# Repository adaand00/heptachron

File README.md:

```
    __  ____________  _________   ________  ______  ____  _   __
   / / / / ____/ __ \/_  __/   | / ____/ / / / __ \/ __ \/ | / /
  / /_/ / __/ / /_/ / / / / /| |/ /   / /_/ / /_/ / / / /  |/ / 
 / __  / /___/ ____/ / / / ___ / /___/ __  / _, _/ /_/ / /|  /  
/_/ /_/_____/_/     /_/ /_/  |_\____/_/ /_/_/ |_|\____/_/ |_/   
```                                                                
## Heptachron - 7 segment LED wrist watch
Latest prototype:

### Concepts and ideas

### Features
 - [x] 4 digits (hours and minutes)
 - [x] Seconds displayed in binary (6 bits)
 - [x] Always-on display
 - [x] Rechargeable battery
 - [x] Magnetic charger
 - [ ] Long battery life
 - [x] Megatron
 - [x] Not waterproof
 - [ ] Very accurate

### Contributors
Adam Anderson: Electronics, programming

Gustav Abrahamsson: Electronics, mechanical design

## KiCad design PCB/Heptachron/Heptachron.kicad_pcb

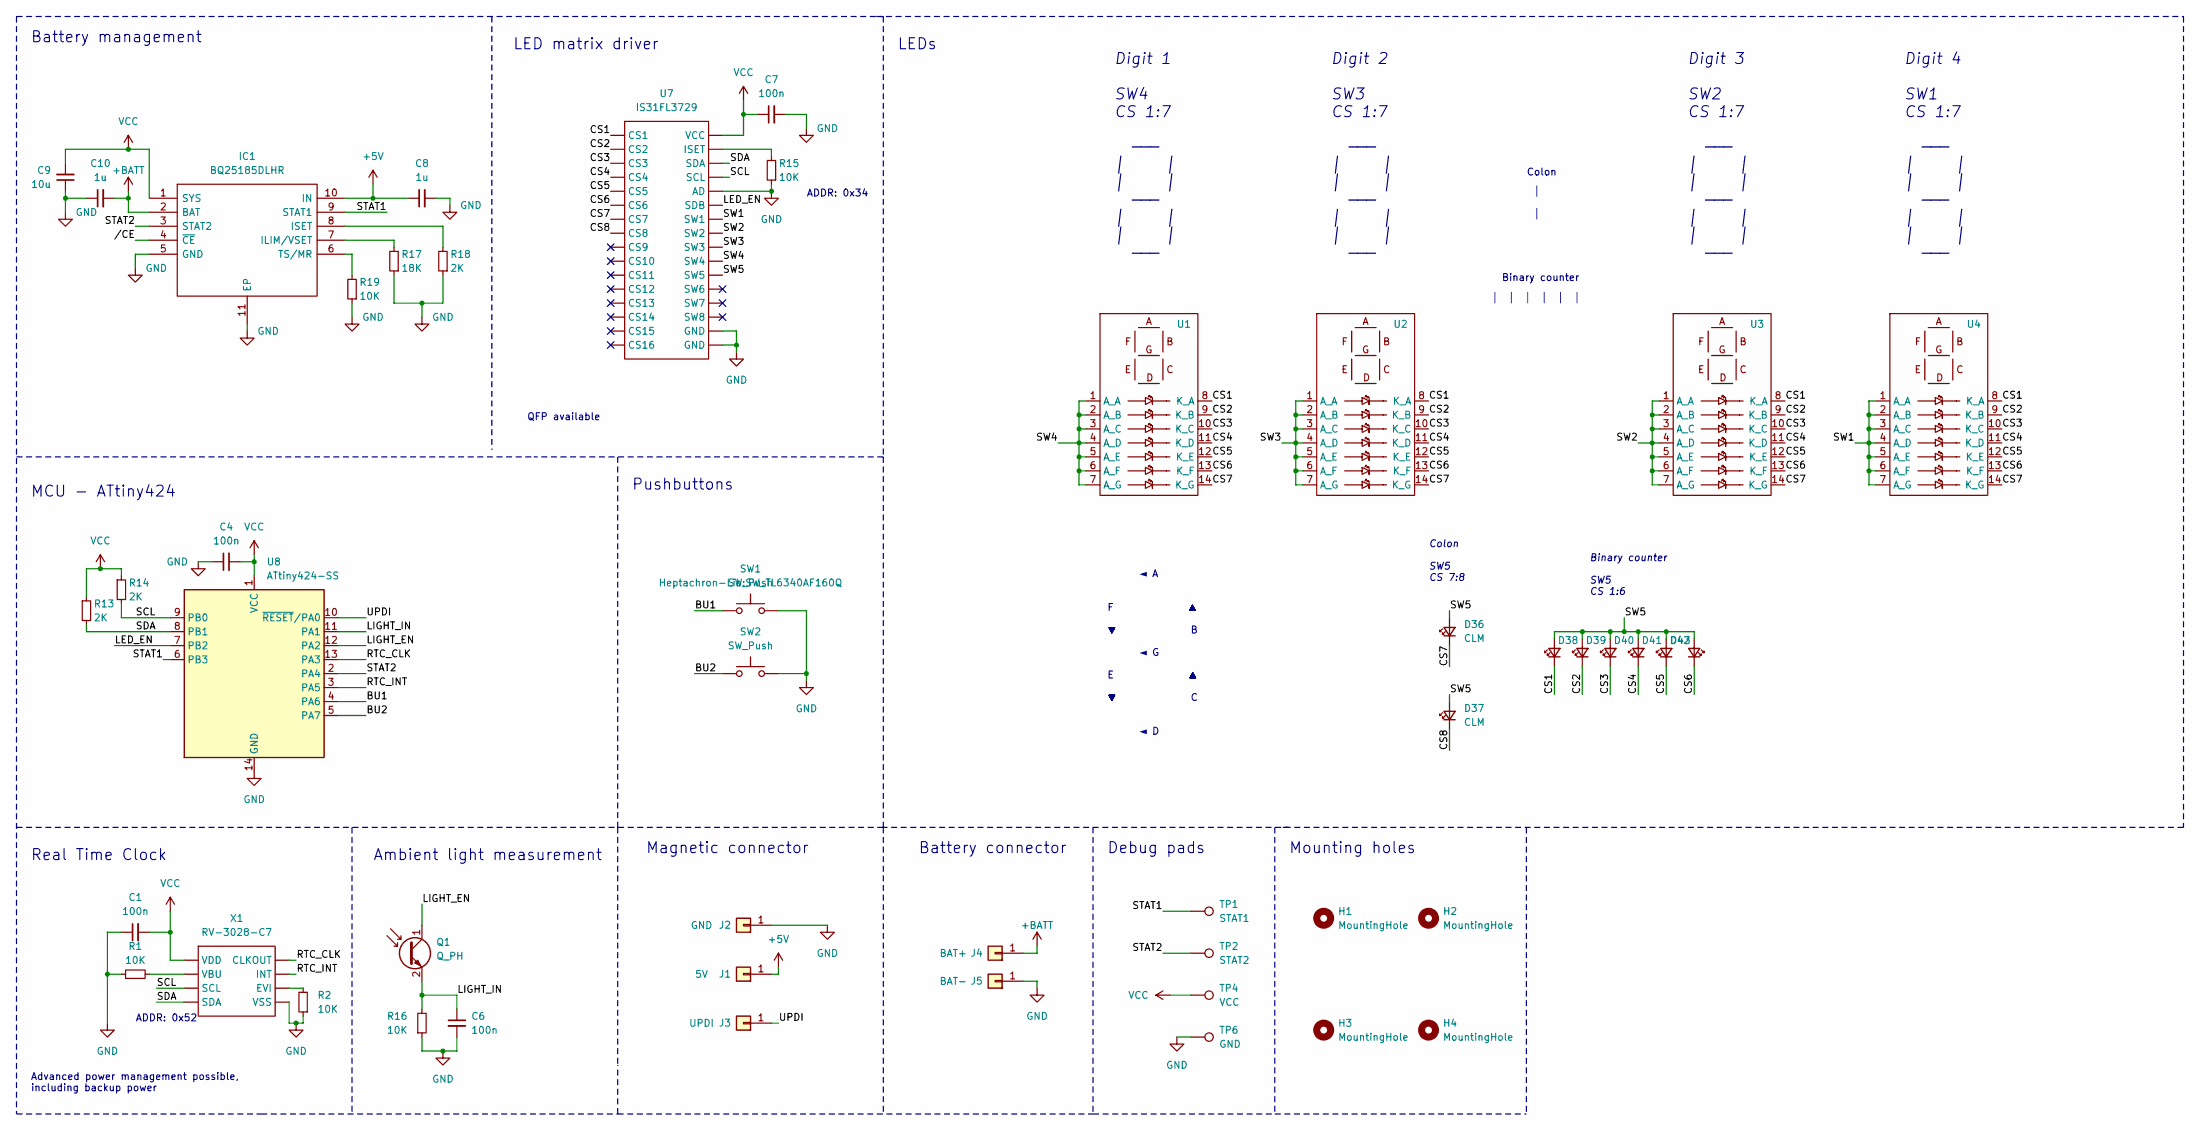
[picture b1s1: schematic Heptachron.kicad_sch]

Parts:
C1, C4, C6, C7: 100n; C_0603_1608Metric
C8, C10: 1u; C_0805_2012Metric
C9: 10u; C_0805_2012Metric
D36, D37: CLM; LED_0603_1608Metric
D38, D39, D40, D41, D42, D43: LED_0603_1608Metric
H1, H2, H3, H4: MountingHole; MountingHole_1.5mm_PAD
IC1: BQ25185DLHR; SON40P220X200X80-11N; Mouser Part Number 595-BQ25185DLHR
J1: 5V; SolderWirePad_1x01_SMD_1x2mm
J2: GND; SolderWirePad_1x01_SMD_1x2mm
J3: UPDI; SolderWirePad_1x01_SMD_1x2mm
J4: BAT+; SolderWirePad_1x01_SMD_1x2mm
J5: BAT-; SolderWirePad_1x01_SMD_1x2mm
Q1: Q_PH; LED_0603_1608Metric
R1, R2, R15, R16, R19: 10K; R_0603_1608Metric
R13, R14, R18: 2K; R_0603_1608Metric
R17: 18K; R_0603_1608Metric
SW1, SW2: SW_Push; SW_TL6340AF160Q
TP1: STAT1; TestPoint_Pad_D1.0mm
TP2: STAT2; TestPoint_Pad_D1.0mm
TP4: VCC; TestPoint_Pad_D1.0mm
TP6: GND; TestPoint_Pad_D1.0mm
U1, U2, U3, U4: 7-SEGMENT_NEW
U7: IS31FL3729; TQFP-32_7x7mm_P0.8mm
U8: ATtiny424-SS; SOIC-14_3.9x8.7mm_P1.27mm
X1: RV-3028-C7

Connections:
+5V: C8.1, IC1.10 (IN), J1.1
+BATT: C10.2, IC1.2 (BAT), J4.1
/BU1: SW1.1, U8.4 (PA6)
/BU2: SW2.1, U8.5 (PA7)
/CS1: D38.1 (K), U1.8 (K_A), U2.8 (K_A), U3.8 (K_A), U4.8 (K_A), U7.30 (CS1)
/CS2: D39.1 (K), U1.9 (K_B), U2.9 (K_B), U3.9 (K_B), U4.9 (K_B), U7.31 (CS2)
/CS3: D40.1 (K), U1.10 (K_C), U2.10 (K_C), U3.10 (K_C), U4.10 (K_C), U7.32 (CS3)
/CS4: D41.1 (K), U1.11 (K_D), U2.11 (K_D), U3.11 (K_D), U4.11 (K_D), U7.1 (CS4)
/CS5: D42.1 (K), U1.12 (K_E), U2.12 (K_E), U3.12 (K_E), U4.12 (K_E), U7.2 (CS5)
/CS6: D43.1 (K), U1.13 (K_F), U2.13 (K_F), U3.13 (K_F), U4.13 (K_F), U7.3 (CS6)
/CS7: D36.1 (K), U1.14 (K_G), U2.14 (K_G), U3.14 (K_G), U4.14 (K_G), U7.4 (CS7)
/CS8: D37.1 (K), U7.5 (CS8)
/LED_EN: U7.29 (SDB), U8.7 (PB2)
/LIGHT_EN: Q1.1 (C), U8.12 (PA2)
/LIGHT_IN: C6.1, Q1.2 (E), R16.2, U8.11 (PA1)
/RTC_CLK: U8.13 (PA3), X1.1 (CLKOUT)
/RTC_INT: U8.3 (PA5), X1.2 (INT)
/SCL: R14.2, U7.27 (SCL), U8.9 (PB0), X1.3 (SCL)
/SDA: R13.2, U7.26 (SDA), U8.8 (PB1), X1.4 (SDA)
/STAT1: IC1.9 (STAT1), TP1.1, U8.6 (PB3)
/STAT2: IC1.3 (STAT2), TP2.1, U8.2 (PA4)
/SW1: U4.1 (A_A), U4.2 (A_B), U4.3 (A_C), U4.4 (A_D), U4.5 (A_E), U4.6 (A_F), U4.7 (A_G), U7.22 (SW1)
/SW2: U3.1 (A_A), U3.2 (A_B), U3.3 (A_C), U3.4 (A_D), U3.5 (A_E), U3.6 (A_F), U3.7 (A_G), U7.21 (SW2)
/SW3: U2.1 (A_A), U2.2 (A_B), U2.3 (A_C), U2.4 (A_D), U2.5 (A_E), U2.6 (A_F), U2.7 (A_G), U7.20 (SW3)
/SW4: U1.1 (A_A), U1.2 (A_B), U1.3 (A_C), U1.4 (A_D), U1.5 (A_E), U1.6 (A_F), U1.7 (A_G), U7.19 (SW4)
/SW5: D36.2 (A), D37.2 (A), D38.2 (A), D39.2 (A), D40.2 (A), D41.2 (A), D42.2 (A), D43.2 (A), U7.18 (SW5)
/UPDI: J3.1, U8.10 (~RESET/PA0)
//CE: IC1.4 (~CE)
GND: C1.1, C4.1, C6.2, C7.2, C8.2, C9.1, C10.1, IC1.5 (GND), IC1.11 (EP), J2.1, J5.1, R1.1, R2.1, R15.1, R16.1, R17.1, R18.1, R19.1, SW1.2, SW2.2, TP6.1, U7.9 (GND), U7.24 (GND), U7.28 (AD), U8.14 (GND), X1.5 (VSS)
unnamed: IC1.7 (ILIM/VSET), R17.2
unnamed: IC1.8 (ISET), R18.2
unnamed: IC1.6 (TS/MR), R19.2
unnamed: R15.2, U7.25 (ISET)
unnamed: R2.2, X1.8 (EVI)
unnamed: R1.2, X1.6 (VBU)
VCC: C1.2, C4.2, C7.1, C9.2, IC1.1 (SYS), R13.1, R14.1, TP4.1, U7.23 (VCC), U8.1 (VCC), X1.7 (VDD)

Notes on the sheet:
Digit 3 SW2 CS 1:7 ─── │ │ │ │ ─── │ │ │ │ ───
Advanced power management possible, including backup power
│ │
Pushbuttons
Digit 2 SW3 CS 1:7 ─── │ │ │ │ ─── │ │ │ │ ───
◄ A F ▲ ▼ B ◄ G E ▲ ▼ C ◄ D
ADDR: 0x34
Real Time Clock
LED matrix driver
Ambient light measurement
QFP available
Magnetic connector
Mounting holes
│ │ │ │ │ │
Battery management
LEDs
Colon
Binary counter
Colon SW5 CS 7:8
Debug pads
Digit 1 SW4 CS 1:7 ─── │ │ │ │ ─── │ │ │ │ ───
ADDR: 0x52
Binary counter SW5 CS 1:6
Battery connector
MCU - ATtiny424
Digit 4 SW1 CS 1:7 ─── │ │ │ │ ─── │ │ │ │ ───

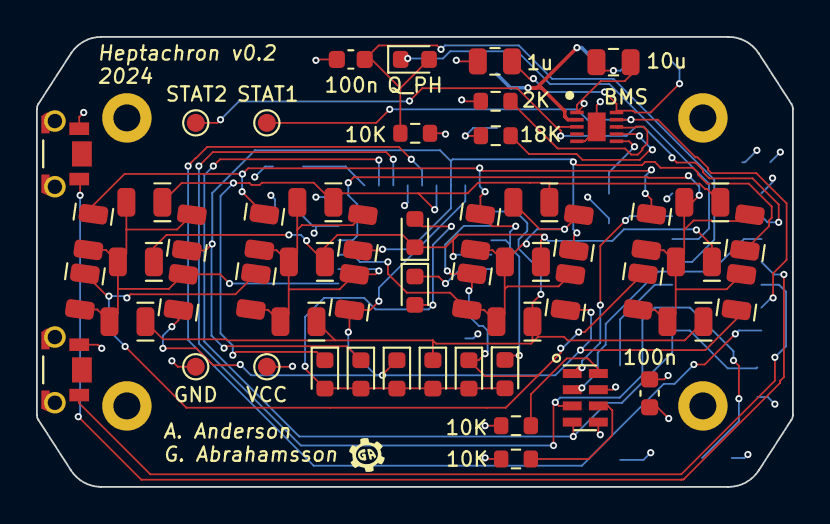
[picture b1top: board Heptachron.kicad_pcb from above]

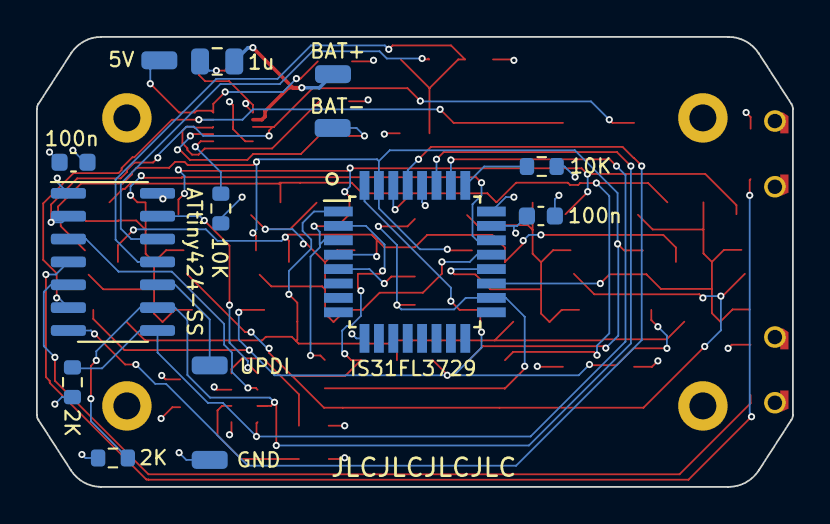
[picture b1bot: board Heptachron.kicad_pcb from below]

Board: 4 copper layers, 42.0 x 25.0 mm, 48 parts (14 on the bottom side), 35 nets.

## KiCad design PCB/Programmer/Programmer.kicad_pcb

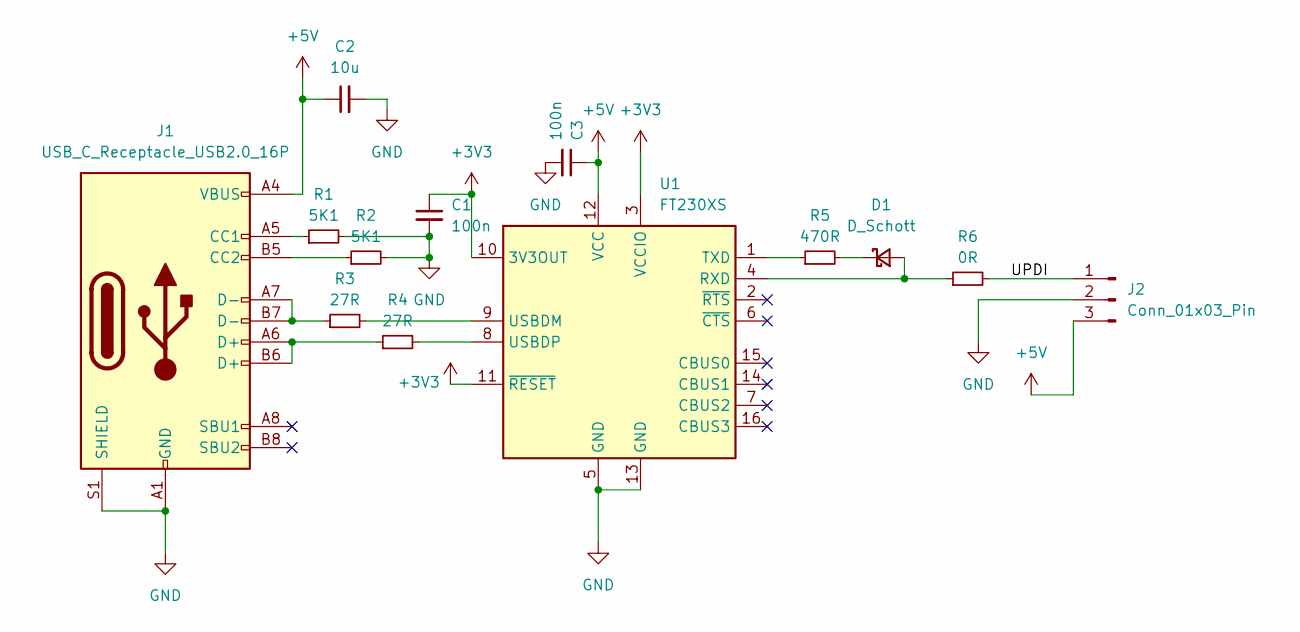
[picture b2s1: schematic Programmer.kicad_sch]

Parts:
C1, C3: 100n; C_0603_1608Metric
C2: 10u; C_0805_2012Metric
D1: D_Schott; D_SOD-323_HandSoldering
J1: USB_C_Receptacle_USB2.0_16P; USB_C_Receptacle_HRO_TYPE-C-31-M-12
J2: Conn_01x03_Pin; PinHeader_1x03_P2.54mm_Vertical
R1, R2: 5K1; R_0603_1608Metric
R3, R4: 27R; R_0603_1608Metric
R5: 470R; R_0603_1608Metric
R6: 0R; R_0603_1608Metric
U1: FT230XS; SSOP-16_3.9x4.9mm_P0.635mm

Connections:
+3V3: C1.1, U1.3 (VCCIO), U1.10 (3V3OUT), U1.11 (~RESET)
+5V: C2.1, C3.1, J1.A4 (VBUS), J1.A9 (VBUS), J1.B4 (VBUS), J1.B9 (VBUS), J2.3, U1.12 (VCC)
/UPDI: J2.1, R6.2
GND: C1.2, C2.2, C3.2, J1.A1 (GND), J1.A12 (GND), J1.B1 (GND), J1.B12 (GND), J1.S1 (SHIELD), J2.2, R1.2, R2.2, U1.5 (GND), U1.13 (GND)
unnamed: D1.2 (A), R6.1, U1.4 (RXD)
unnamed: D1.1 (K), R5.2
unnamed: J1.A5 (CC1), R1.1
unnamed: J1.B5 (CC2), R2.1
unnamed: J1.A6 (D+), J1.B6 (D+), R4.1
unnamed: J1.A7 (D-), J1.B7 (D-), R3.1
unnamed: R5.1, U1.1 (TXD)
unnamed: R3.2, U1.9 (USBDM)
unnamed: R4.2, U1.8 (USBDP)

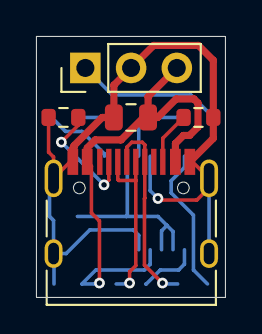
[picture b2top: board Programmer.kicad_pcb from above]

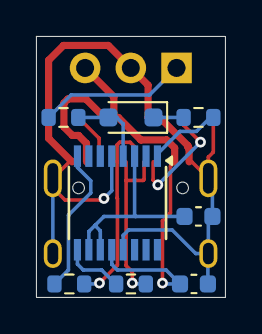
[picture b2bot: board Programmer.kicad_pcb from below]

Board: 2 copper layers, 10.5 x 14.5 mm, 13 parts (8 on the bottom side), 13 nets.

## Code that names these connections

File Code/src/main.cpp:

#include <Arduino.h>
#include "Wire.h"
#include "avr/sleep.h"

#include "LedMatrix.h"
#include "RV3028C7.h"

#define SCL PIN_PB0
#define SDA PIN_PB1

#define LED_EN PIN_PB2

#define RTC_CLK PIN_PA3
#define RTC_INT PIN_PA5

#define LIGHT_IN PIN_PA1
#define LIGHT_EN PIN_PA2

#define STAT1 PIN_PB3
#define STAT2 PIN_PA4

#define BU1 PIN_PA6
#define BU2 PIN_PA7

#define LED_ADDR 0x34
#define RTK_ADDR 0x52

LedMatrix mat(&Wire);
RV3028C7 rtc;

typedef enum screens {
  TIME,
  BAT,
  // BRIGHTNESS,
  SCREENS_MAX,
} screen_t;

screen_t screen;
uint8_t edit = false;

uint8_t idle_count;

int bat = 0;
int light = 0;
volatile int i = 0;

// Overwrite TCA0 init since we do not use analogWrite(), saves some flash 
void init_TCA0() { };

void setup() {
  // Setup sleep mode
  set_sleep_mode(SLEEP_MODE_PWR_DOWN);
  sleep_enable();
  
  // Setup pins
  pinMode(LIGHT_EN, OUTPUT);
  digitalWriteFast(LIGHT_EN, LOW);
  pinMode(LIGHT_IN, INPUT);

  pinMode(BU1, INPUT_PULLUP);
  PORTA_PIN6CTRL |= PORT_ISC_BOTHEDGES_gc;

  pinMode(BU2, INPUT_PULLUP);
  PORTA_PIN7CTRL |= PORT_ISC_BOTHEDGES_gc;

  pinMode(LED_EN, OUTPUT);
  digitalWriteFast(LED_EN, HIGH);

  //pinMode(PGOOD, INPUT_PULLUP);
  //pinMode(RX, INPUT_PULLUP);
  //pinMode(TX, INPUT_PULLUP);

  // Clock pin interrupts
  pinMode(RTC_CLK, INPUT);
  PORTA_PIN3CTRL |= PORT_ISC_BOTHEDGES_gc;

  // Set fixed adc reference
  analogReference(INTERNAL1V024);
  // Disable ADC before sleep, brings system from 100 uA to 10 uA deep sleep.
  ADC0.CTRLA &= ~ADC_ENABLE_bm;

  // I2C 
  Wire.begin();
  Wire.setClock(400000);

  // LED matrix driver
  mat.begin();

  // RTC 
  rtc.begin(Wire);
  rtc.disableClockOutput();
  delay(1000);
  rtc.enableClockOutput(CLKOUT_1HZ);

  // init state
  screen = TIME;
}

ISR(PORTA_PORT_vect){
  int f = VPORTA_INTFLAGS;

  if(f == 1<<6){
    // Button 1
    VPORTA_INTFLAGS |= 1<<6;
  }
  if(f == 1<<7){
    // Button 2
    VPORTA_INTFLAGS |= 1<<7;
  }
  if(f == 1<<3){
    // RTC 
    i++;
    VPORTA_INTFLAGS |= 1<<3;
  }
}

void loop() {
  // Waits until pin change interrupt
  // Either RTC tick or button press
  sleep_cpu(); 
  // Increment wakeup count

  
  //Enable ADC after being woken up
  ADC0.CTRLA |= ADC_ENABLE_bm;
  // Read battery voltage, int v = 1024*VDD/10
  bat = analogRead(ADC_VDDDIV10);

  /*
  if(bat < 370){
    state = BUVLO;
  }
  */

  // Start phototransistor 
  digitalWriteFast(LIGHT_EN, HIGH);
  delay(2);

  // Read phototransistor
  light = analogRead(LIGHT_IN);
  digitalWriteFast(LIGHT_EN, LOW);
  // Turn off ADC
  ADC0.CTRLA &= ~ADC_ENABLE_bm;

  //mat.ShowBytes(255, 255, 255, 255, 255);
  
  // Read buttons
  bool b1 = !digitalReadFast(BU1);
  bool b2 = !digitalReadFast(BU2);

  // b1 goes to next screen;
  if(!edit && b1){
    screen = (screen_t) ((screen+1) % SCREENS_MAX);
  }

  switch (screen)
  {
  case TIME:
    // Read time and update LEDs
    rtc.updateTime();
    uint8_t h = rtc.getDateTimeComponent(DATETIME_HOUR);
    uint8_t m = rtc.getDateTimeComponent(DATETIME_MINUTE);
    uint8_t s = rtc.getDateTimeComponent(DATETIME_SECOND);

    // Go to next edit
    if(b2){
      edit = (edit+1)%3;
    }
    
    if(edit==1){
      // Edit minutes
      m=(m+b1)%60;
      rtc.setDateTimeComponent(DATETIME_MINUTE, m);
      rtc.synchronize();
      rtc.setDateTimeComponent(DATETIME_SECOND, 0);
      rtc.synchronize();
      
      // Blink minutes
      if(i%2 == 0){
        m = 255;
      }
      
    }else if(edit==2){
      // Edit hours 
      h=(h+b1)%24;
      rtc.setDateTimeComponent(DATETIME_HOUR, h);
      rtc.synchronize();
      rtc.setDateTimeComponent(DATETIME_SECOND, 0);
      rtc.synchronize();

      if(i%2 == 0){
        h = 255;
      }
    }

    mat.ShowTime(h, m, s, i%2);
    break;

  case BAT:
    uint8_t t = 0;
    mat.ShowBytes(0b01111100,0b01110111,0b01111000,0,t);

    if(b1){
      // Toggle LEDs on/off
      digitalWriteFast(LED_EN, !digitalReadFast(LED_EN));
    }
    break;

  default:
    break;
  }
  


}

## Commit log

2024-02-22 Start PCB
2024-02-23 More PCB work
2024-03-07 LEDs and more
2024-03-09 Continue schematic
2024-03-09 Continue schematic, symbols & footprints for digits
2024-03-09 PCB work and 3D modeling
2024-03-10 Finish test PCB [Ordered]
2024-03-21 Work on schematic
2024-03-24 Continue design
2024-03-24 Test PCB finished!
2024-04-02 Create Platformio project
2024-04-02 Pins
2024-04-06 Led driver code
2024-04-07 Add testing PCB [Ordered]
2024-04-08 Untested code for RTC
2024-04-11 Clock output finally working
2024-04-12 RTC functions
2024-04-16 Continue PCB
2024-04-18 Button inputs and 10 uA sleep!
2024-04-20 Programmer finished
2024-04-20 Add stl and step
2024-04-20 PCB v0.1 [Ordered]
2024-04-21 Programmer Gerbers
2024-05-04 Optimize code and change upload tool
2024-05-11 PCB v0.2
2024-05-24 Add BOM and misc
2024-05-30 Update to 824
2024-06-05 reverse seconds bits, blinking not working
2024-11-16 Add pictures and GIFs
2024-11-16 Add v2 case and connector
